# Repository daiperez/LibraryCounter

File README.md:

# LibraryCounter
a hardware device and software system for counting library visitors at Pacific University

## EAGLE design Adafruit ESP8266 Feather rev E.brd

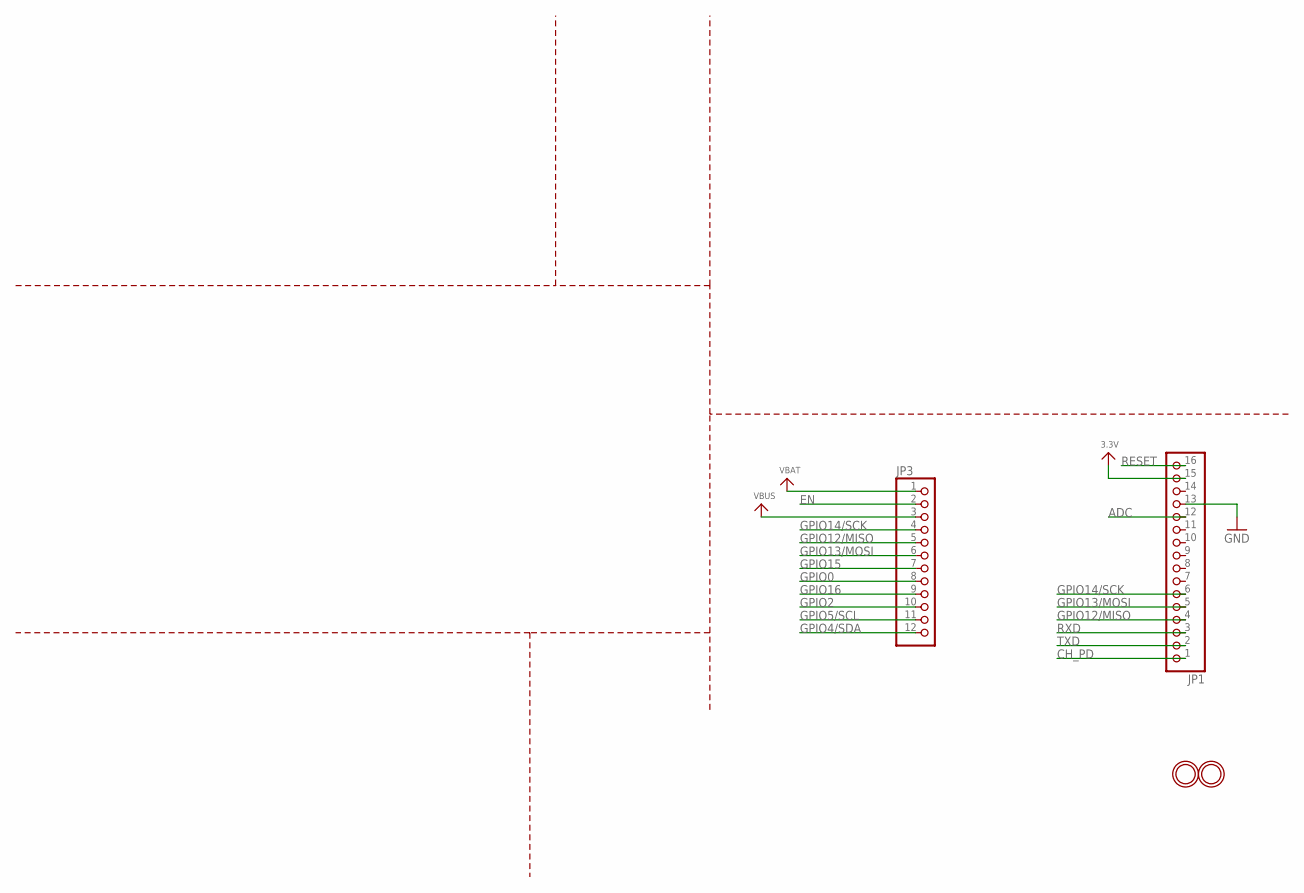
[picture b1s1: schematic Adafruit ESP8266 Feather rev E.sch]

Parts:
JP1: HEADER-1X16ROUND; 1X16_ROUND
JP3: HEADER-1X12; 1X12_ROUND
U$31, U$32: MOUNTINGHOLE2.5; MOUNTINGHOLE_2.5_PLATED

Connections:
3.3V: JP1.15
ADC: JP1.12
CH_PD: JP1.1
EN: JP3.2
GND: JP1.13
GPIO0: JP3.8
GPIO2: JP3.10
GPIO4/SDA: JP3.12
GPIO5/SCL: JP3.11
GPIO12/MISO: JP1.4, JP3.5
GPIO13/MOSI: JP1.5, JP3.6
GPIO14/SCK: JP1.6, JP3.4
GPIO15: JP3.7
GPIO16: JP3.9
RESET: JP1.16
RXD: JP1.3
TXD: JP1.2
VBAT: JP3.1
VBUS: JP3.3

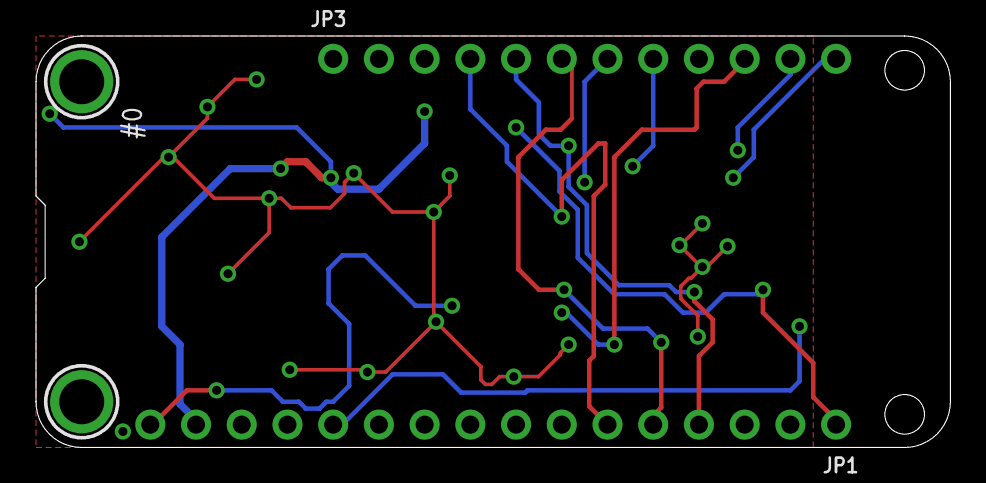
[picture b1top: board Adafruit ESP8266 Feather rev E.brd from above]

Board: 2 copper layers, 50.8 x 22.9 mm, 4 parts (0 on the bottom side), 3 nets.

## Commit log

2020-06-24 Uploaded Schematic and Board
    I uploaded files that pertain to the in-progress wing.
2020-07-08 Added Jupyter Notebook, started code
    I added a jupyter notebook to my branch and it is a general gameplan for our code.
    I have added some .h file code to the jupyter notebook aswell.

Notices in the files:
parts and their libraries:
microbuilder: This work is placed in the public domain, and may be freely used for commercial and non-commercial work with the following conditions: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
